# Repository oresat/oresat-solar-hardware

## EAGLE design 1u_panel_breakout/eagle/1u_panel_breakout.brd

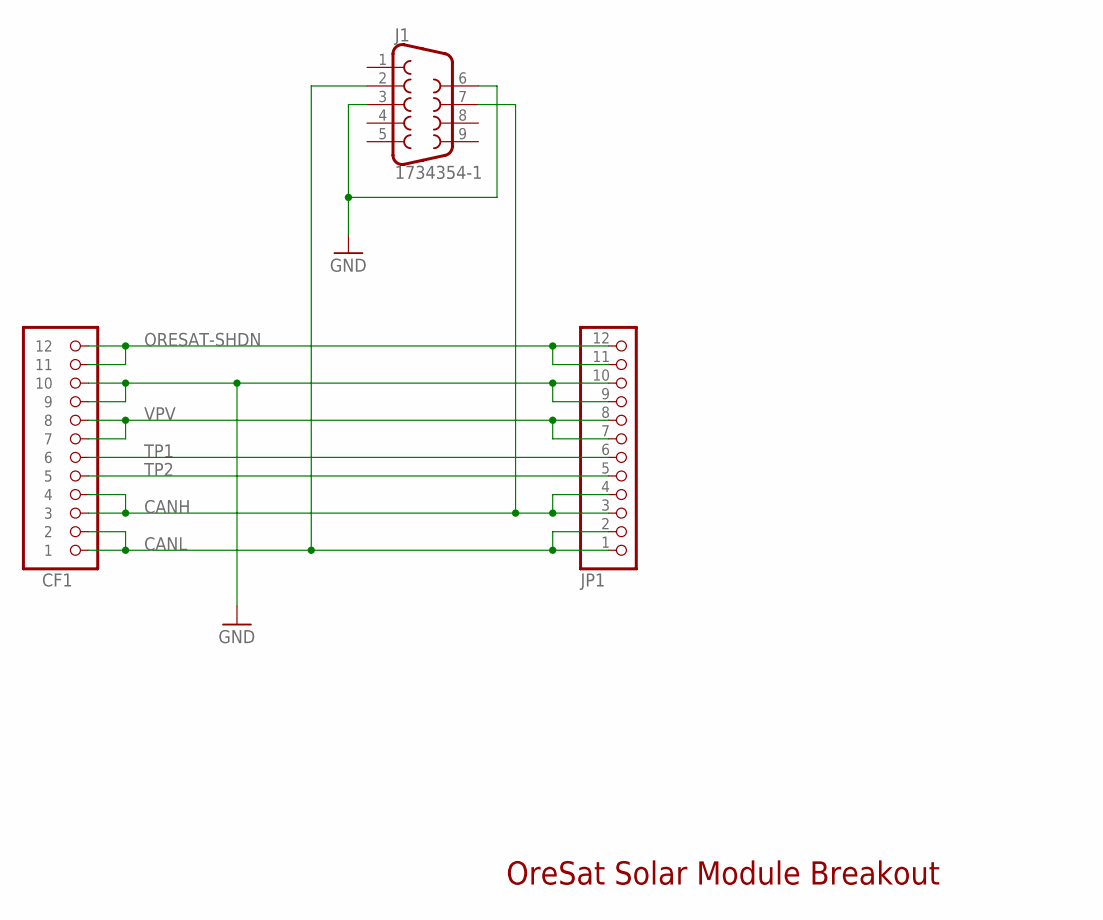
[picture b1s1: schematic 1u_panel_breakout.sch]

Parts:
CF1: ORESAT-SOLARPANEL-12PIN; CON-1.27-F-HARTING-1522012X601XXX
J1: 1734354-1; TE_1734354-1
JP1: PINHD-1X12; 1X12

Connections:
CANH: CF1.3, CF1.4, J1.7, JP1.3, JP1.4
CANL: CF1.1, CF1.2, J1.2, JP1.1, JP1.2
GND: CF1.9, CF1.10, J1.3, J1.6, JP1.9, JP1.10
ORESAT-SHDN: CF1.11, CF1.12, JP1.11, JP1.12
TP1: CF1.6, JP1.6
TP2: CF1.5, JP1.5
VPV: CF1.7, CF1.8, JP1.7, JP1.8

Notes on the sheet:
OreSat Solar Module Breakout

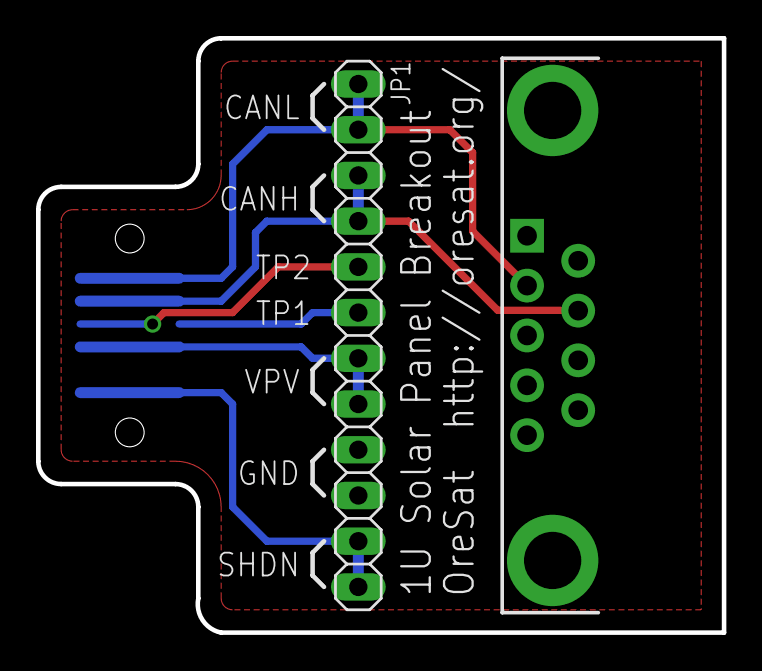
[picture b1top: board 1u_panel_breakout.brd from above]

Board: 2 copper layers, 38.1 x 33.0 mm, 3 parts (1 on the bottom side), 7 nets.

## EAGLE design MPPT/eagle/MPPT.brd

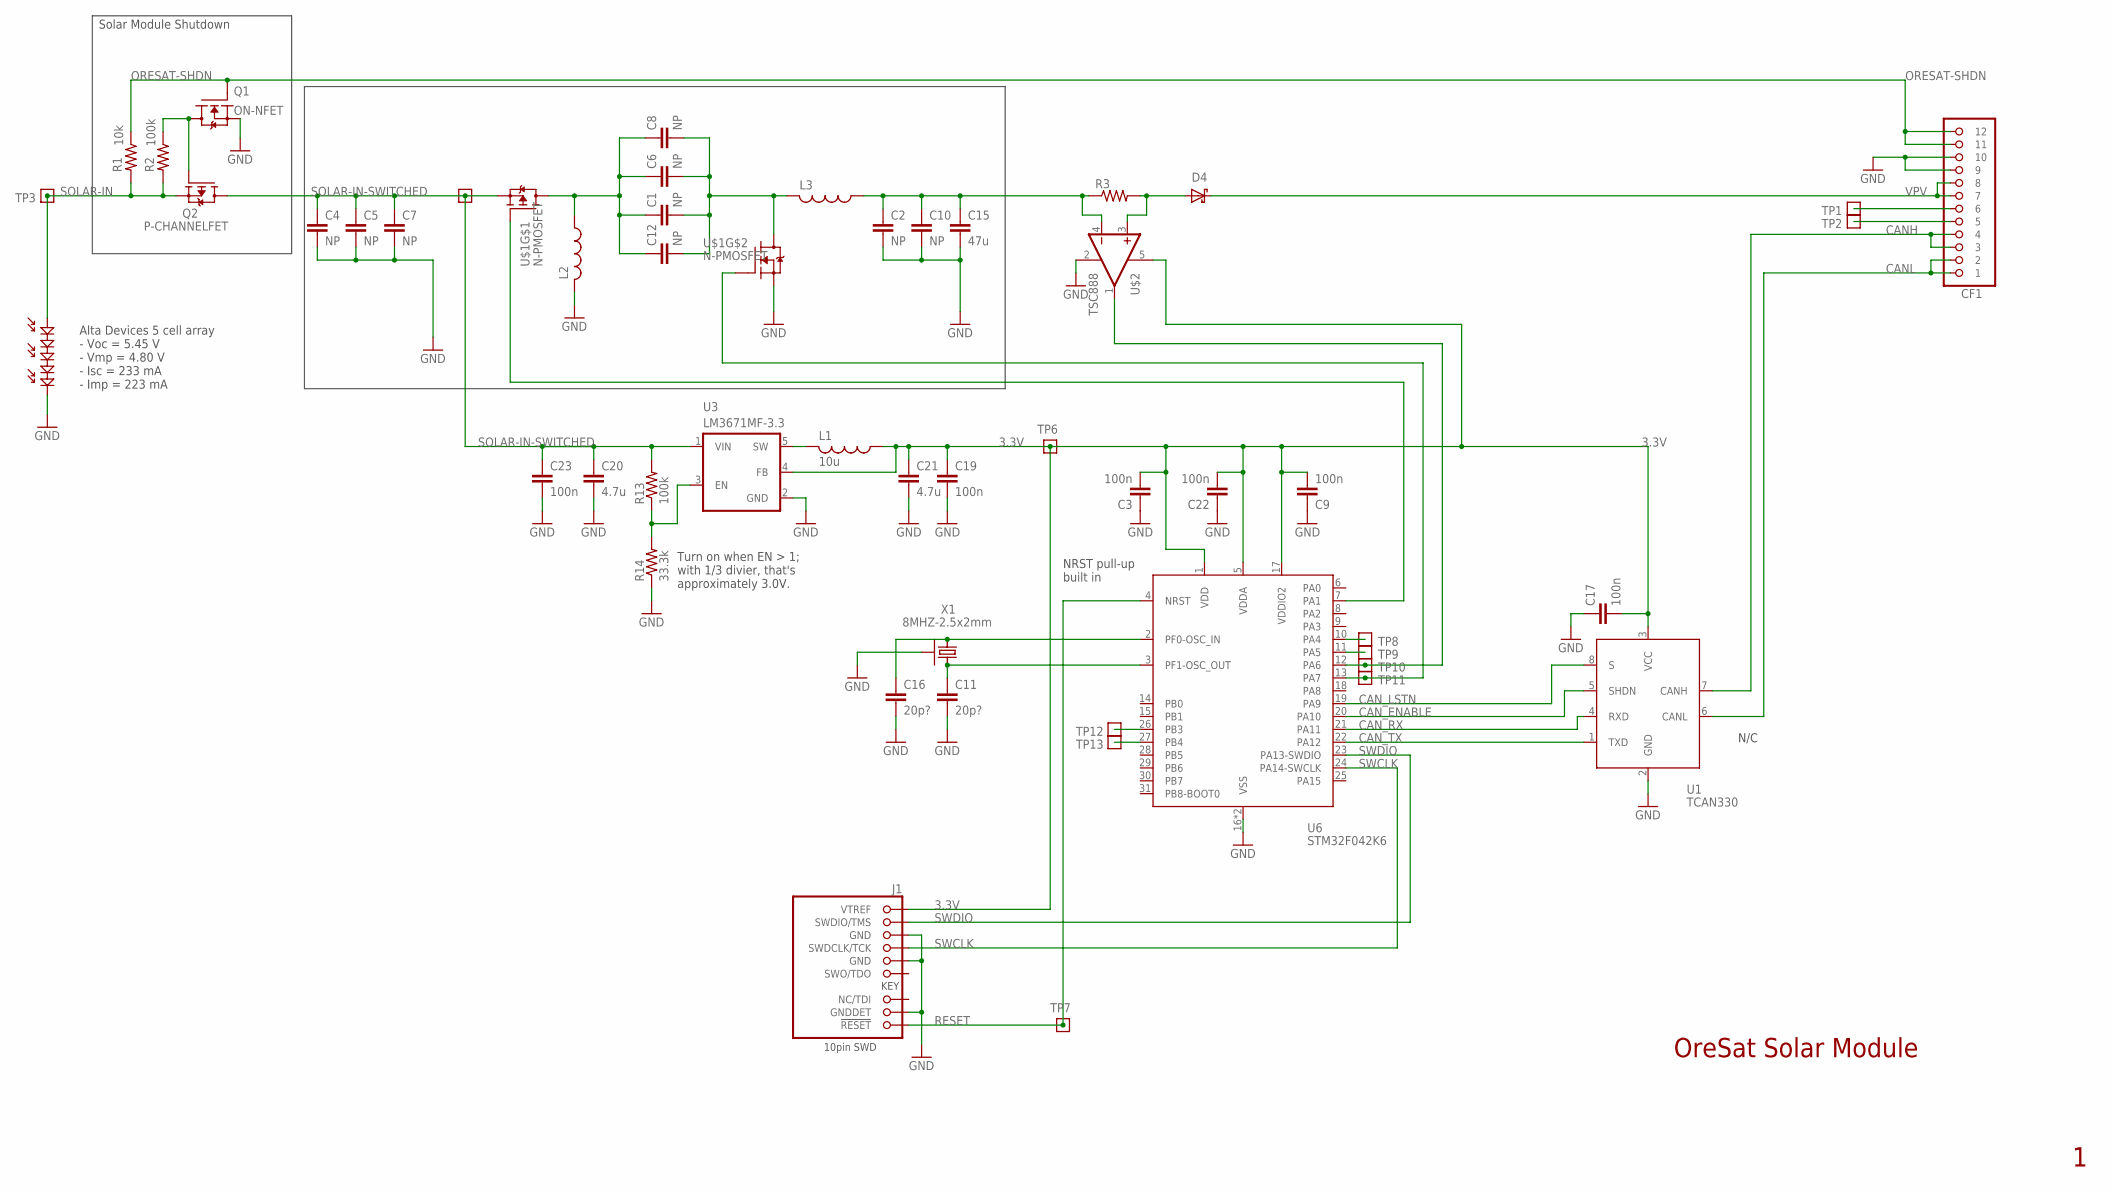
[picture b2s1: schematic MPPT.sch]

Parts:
C1, C2, C4, C5, C6, C7, C8, C10, C12: NP; C0603
C3, C9, C17, C19, C22, C23: 100n; .0402-B-NOSILK
C11, C16: 20p?; .0402-B-NOSILK
C15: 47u; C0603
C20, C21: 4.7u; C0603
CF1: ORESAT-SOLARPANEL-12PIN; CON-1.27-F-HARTING-1522012X601XXX
D2: ALTA-5-CELL-ARRAY; ALTA-FIVE-CELL
D4: SOD123-B SCHOTTKY; SOD123-B
J1: 1.27MM-SWD-CONNECTOR; 1.27MM_2X5
L1: 10u; L2012C
L2, L3: L-USL1812; L1812
Q1: ON-NFET; SOT23
Q2: P-CHANNELFET; SO8
R1: 10k; .0402-B-NOSILK
R2, R13: 100k; .0402-B-NOSILK
R3: R-US_R0603; R0603
R14: 33.3k; .0402-B-NOSILK
TP1, TP2, TP3, TP4, TP6, TP7, TP8, TP9, TP10, TP11, TP12, TP13: TEST-POINT; 2MM-TEST-POINT
U1: TCAN330; SOT23-8_TI-DCN
U3: LM3671MF-3.3; SOT23-5
U6: STM32F042K6; QFP32-7X7
U$1: N-PMOSFET; 5X6POWERFLAT
U$2: TSC888; SOT23-5
X1: 8MHZ-2.5x2mm; CRYSTAL_2.5X2

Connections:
3.3V: C3.2, C9.2, C17.2, C19.1, C21.1, C22.2, J1.VTREF, L1.1, TP6.1, U1.3 (VCC), U3.4 (FB), U6.1 (VDD), U6.5 (VDDA), U6.17 (VDDIO2), U$2.5 (V+)
CANH: CF1.3, CF1.4, U1.7 (CANH)
CANL: CF1.1, CF1.2, U1.6 (CANL)
CAN_ENABLE: U1.5 (SHDN), U6.20 (PA10)
CAN_LSTN: U1.8 (S), U6.19 (PA9)
CAN_RX: U1.4 (RXD), U6.21 (PA11)
CAN_TX: U1.1 (TXD), U6.22 (PA12)
CRYSTALIN: C16.1, U6.2 (PF0-OSC_IN), X1.1
CRYSTALOUT: C11.1, U6.3 (PF1-OSC_OUT), X1.3 (2)
GND: C2.2, C3.1, C4.2, C5.2, C7.2, C9.1, C10.2, C11.2, C15.2, C16.2, C17.1, C19.2, C20.2, C21.2, C22.1, C23.2, CF1.9, CF1.10, D2.NEG, J1.GND, J1.GND@2 (GND), J1.GNDDET, L2.2, Q1.2 (S), R14.1, U1.2 (GND), U3.2 (GND), U6.16 (VSS), U6.32 (VSS), U$1.S2 (S), U$2.2 (GND), X1.2 (SHIELD), X1.4 (SHIELD)
N6: Q1.3 (D), Q2.4 (G), R2.1
unnamed: C1.1, C6.1, C8.1, C12.1, L2.1, U$1.D1 (D), U$1.D11 (D), U$1.D12 (D), U$1.D13 (D), U$1.D14 (D)
unnamed: C1.2, C6.2, C8.2, C12.2, L3.2, U$1.D2 (D), U$1.D21 (D), U$1.D22 (D), U$1.D23 (D), U$1.D24 (D)
unnamed: CF1.6, TP1.1
unnamed: CF1.5, TP2.1
unnamed: TP8.1, U6.10 (PA4)
unnamed: TP9.1, U6.11 (PA5)
unnamed: TP10.1, U6.12 (PA6), U$2.1 (OUT)
unnamed: TP11.1, U6.13 (PA7), U$1.G2 (G)
unnamed: TP12.1, U6.26 (PB3)
unnamed: TP13.1, U6.27 (PB4)
unnamed: C2.1, C10.1, C15.1, L3.1, R3.1, U$2.4 (-IN)
unnamed: U6.7 (PA1), U$1.G1 (G)
unnamed: D4.A (ANODE), R3.2, U$2.3 (+IN)
ORESAT-SHDN: CF1.11, CF1.12, Q1.1 (G), R1.1
RESET: J1.!RESET, TP7.1, U6.4 (NRST)
SOLAR-IN: D2.POS, Q2.1 (S), Q2.2 (S), Q2.3 (S), R1.2, R2.2, TP3.1
SOLAR-IN-SWITCHED: C4.1, C5.1, C7.1, C20.1, C23.1, Q2.5 (D), Q2.6 (D), Q2.7 (D), Q2.8 (D), R13.2, TP4.1, U3.1 (VIN), U$1.S1 (S)
STEPD: L1.2, U3.5 (SW)
SWCLK: J1.SWDCLK (SWDCLK/TCK), U6.24 (PA14-SWCLK)
SWDIO: J1.SWDIO (SWDIO/TMS), U6.23 (PA13-SWDIO)
VDIV: R13.1, R14.2, U3.3 (EN)
VPV: CF1.7, CF1.8, D4.K (CATHODE)

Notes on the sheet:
Alta Devices 5 cell array - Voc = 5.45 V - Vmp = 4.80 V - Isc = 233 mA - Imp = 223 mA
N/C
NRST pull-up built in
Turn on when EN > 1; with 1/3 divier, that's approximately 3.0V.
OreSat Solar Module
Solar Module Shutdown

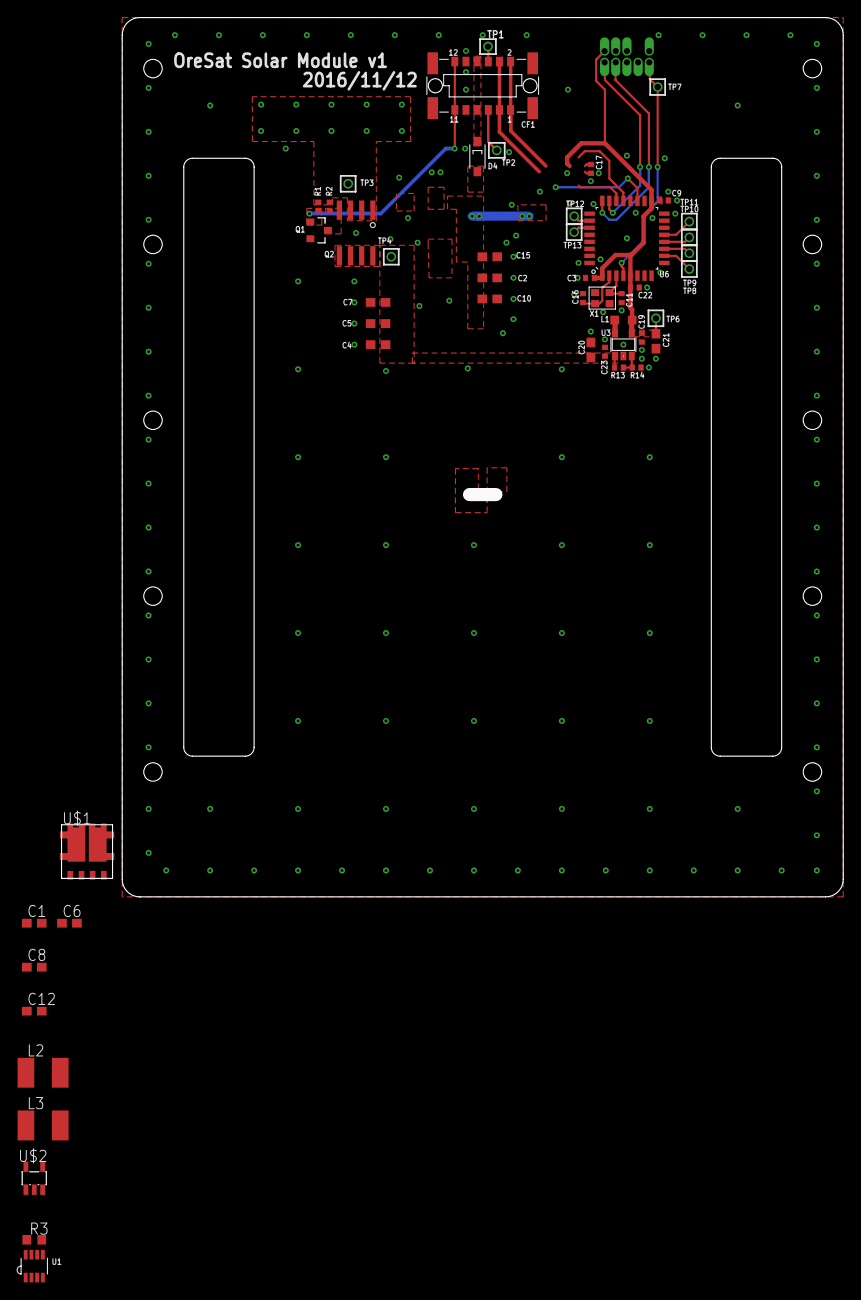
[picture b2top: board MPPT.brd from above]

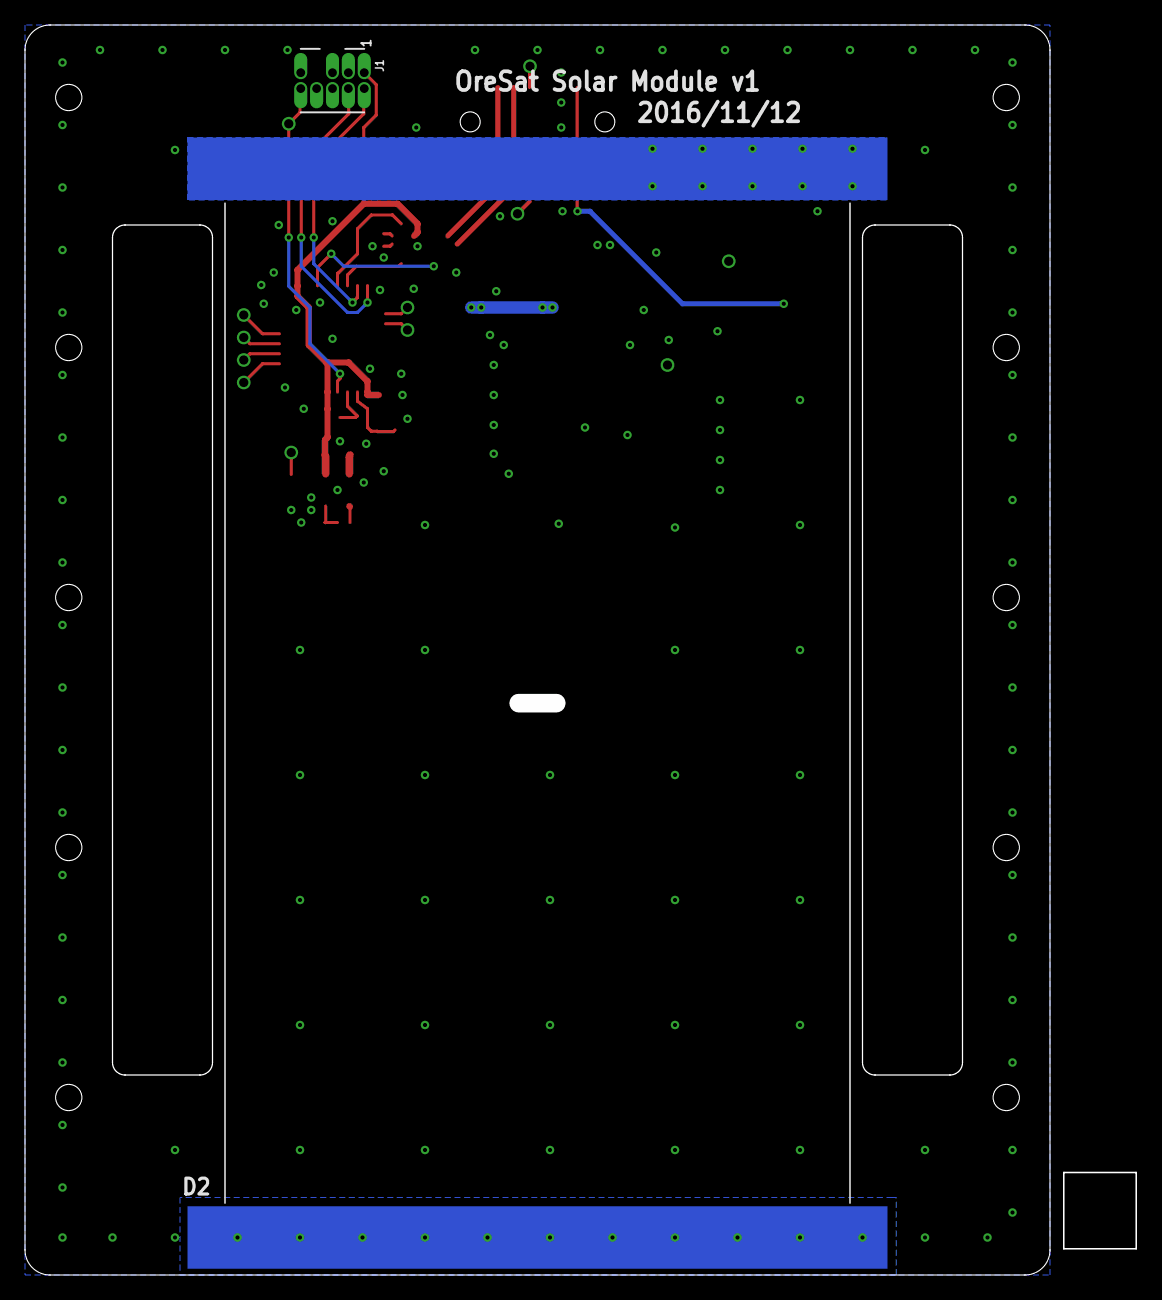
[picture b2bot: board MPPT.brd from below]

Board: 2 copper layers, 88.9 x 100.0 mm, 52 parts (2 on the bottom side), 33 nets.

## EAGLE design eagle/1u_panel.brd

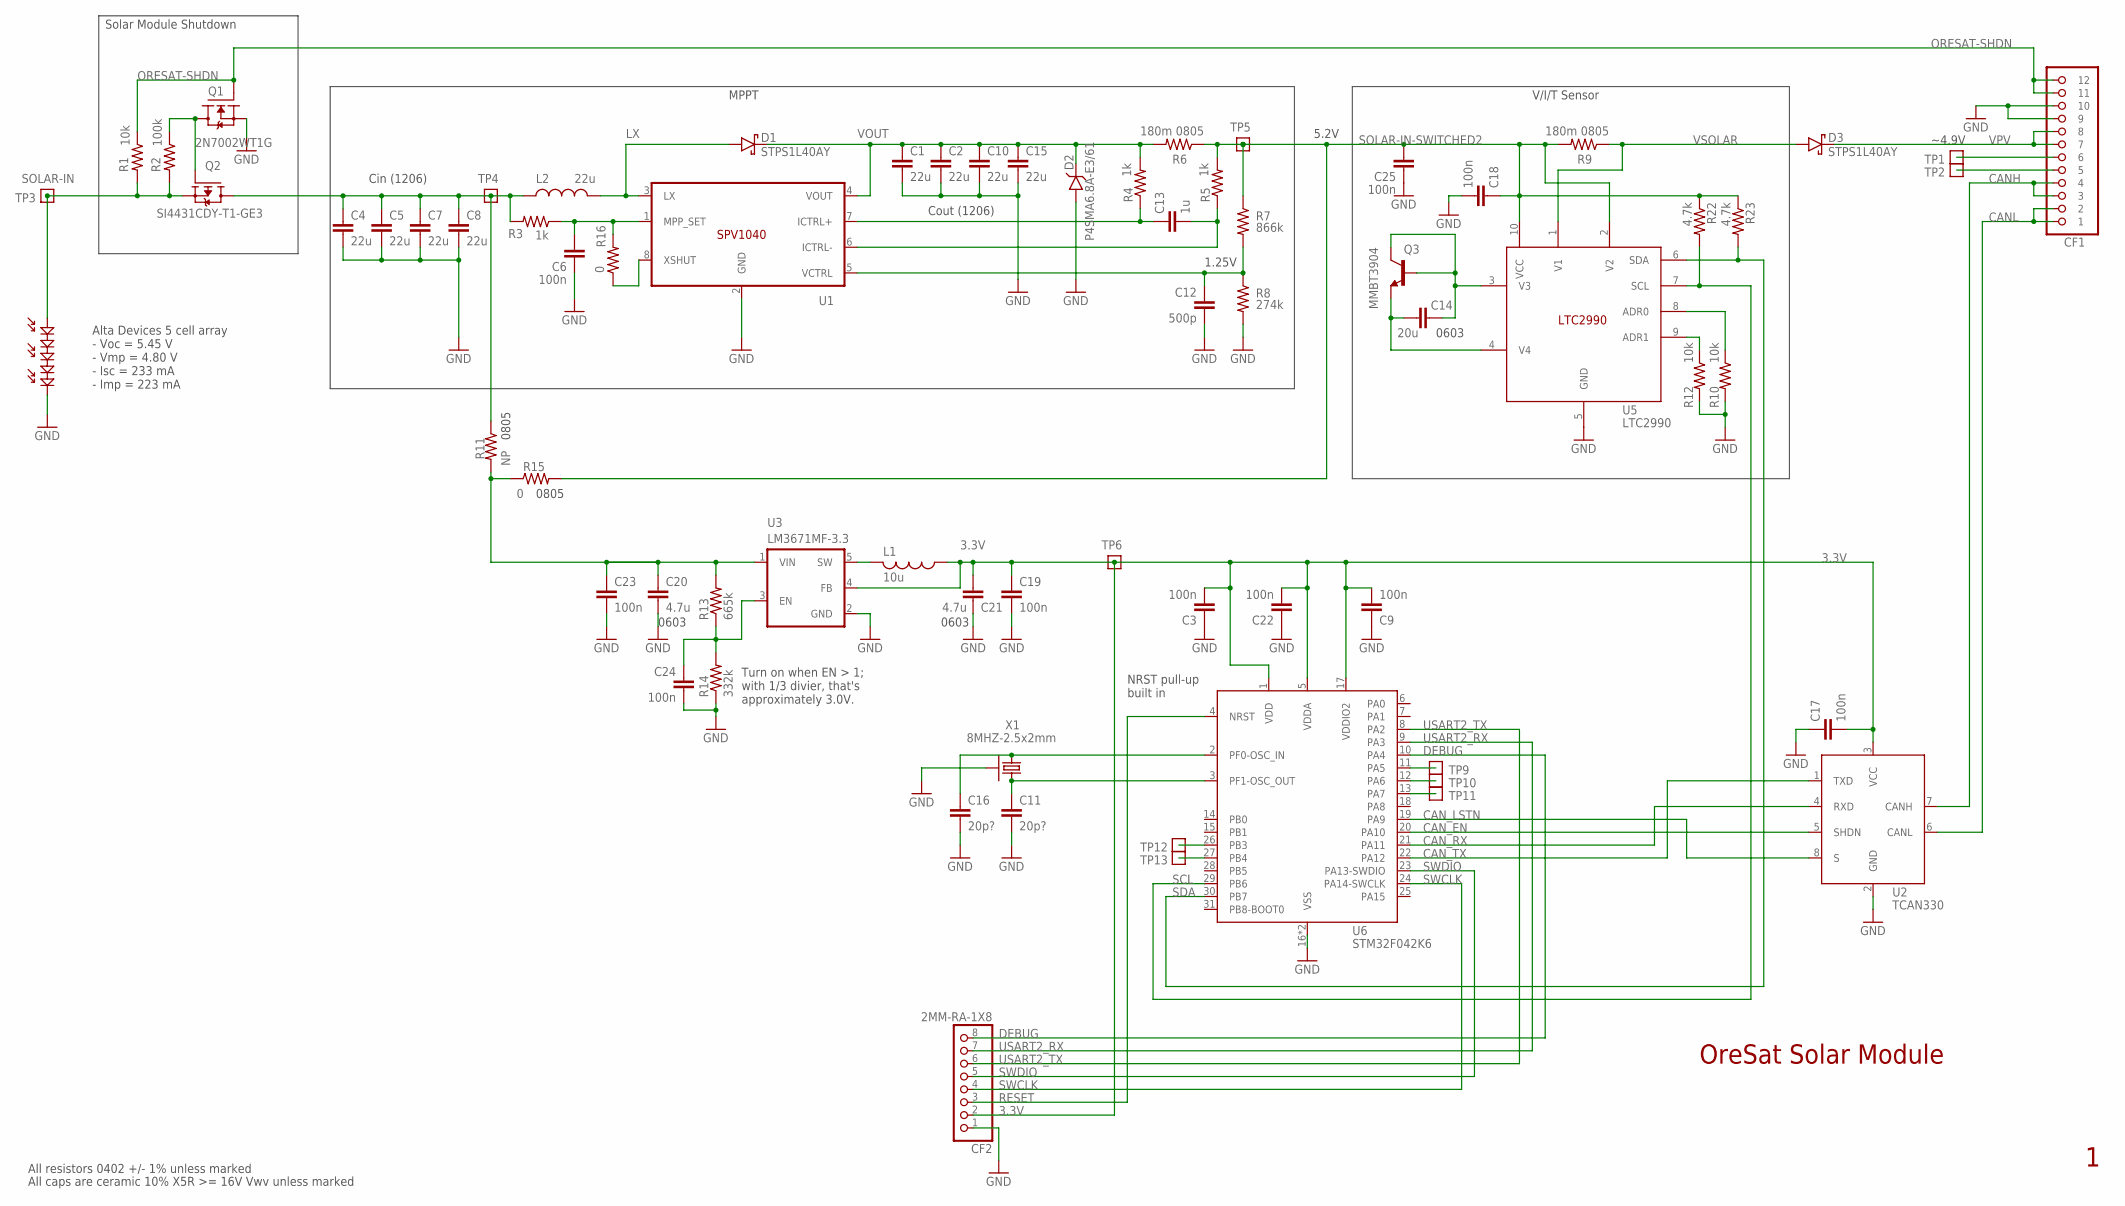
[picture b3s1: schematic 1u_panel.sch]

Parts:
C1, C2, C4, C5, C7, C8, C10, C15: 22u; 1206-B; MPN GRM31CR71A226KE15L
C3, C6, C9, C17, C18, C19, C22, C23, C24, C25: 100n; .0402-B-NOSILK; MPN CL05B104KO5NNNC
C11, C16: 20p?; .0402-B-NOSILK
C12: 500p; .0402-B-NOSILK; MPN CL05B561KB5NNNC
C13: 1u; .0402-B-NOSILK; MPN CL05A105KA5NQNC
C14: 20u; .0603-B-NOSILK; MPN CL10A226MP8NUNE
C20, C21: 4.7u; C0603; MPN CL05B104KO5NNNC
CF1: ORESAT-SOLARPANEL-12PIN; CON-1.27-F-HARTING-1522012X601XXX
CF2: 2MM-RA-1X8; CF-2MM-RA-1X8-PRECIDIP-831; MPN 831-87-050-40-001101
D1, D3: STPS1L40AY; DO214AC; MPN STPS1L40AY
D2: P4SMA6.8A-E3/61; DO214AC; MPN P4SMA6.8A-E3/61
L1: 10u; L2012C; MPN CB2012T100KR
L2: 22u; VISHAY-DALE-IFSR-1515AHER; MPN IFSC1515AHER220M01
PV1: ALTA-5-CELL-ARRAYALTA-FIVE-CELL-SLOT; ALTA-FIVE-CELL-THROUGH-SLOT
Q1: 2N7002WT1G; SOT23; MPN 2N7002WT1G
Q2: SI4431CDY-T1-GE3; SO8; MPN SI4431CDY-T1-GE3
Q3: MMBT3904; SOT23HOLE; MPN MMBT3904
R1, R10, R12: 10k; .0402-B-NOSILK; MPN MCR01MZPF1002
R2: 100k; .0402-B-NOSILK; MPN MCR01MRTF1003
R3: 1k; .0402-B-NOSILK; MPN MCR01MZPF1001
R4, R5: 1k; .0402-B-NOSILK
R6, R9: 180m 0805; .0805-B-NOSILK; MPN RCWE0805R180FKEA
R7: 866k; .0402-B-NOSILK; MPN RC1005F8663CS
R8: 274k; .0402-B-NOSILK; MPN CRCW0402274KFKED
R11: NP; .0805-B-NOSILK
R13: 665k; .0402-B-NOSILK; MPN RC1005F6653CS
R14: 332k; .0402-B-NOSILK; MPN RC1005F3323CS
R15: 0; .0805-B-NOSILK
R16: 0; .0402-B-NOSILK
R22, R23: 4.7k; .0402-B-NOSILK; MPN TRR01MZPF4701
TP1, TP2, TP3, TP4, TP5, TP6, TP9, TP10, TP11, TP12, TP13: TEST-POINT; 2MM-TEST-POINT
U1: SPV1040; TSSOP-8; MPN SPV1040T
U2: TCAN330; SOT23-8_TI-DCN; MPN TCAN330GDCNT
U3: LM3671MF-3.3; SOT23-5
U5: LTC2990; MSOP10; MPN LTC2990CMS#PBF
U6: STM32F042K6; QFP32-7X7; MPN STM32F042K6T6
X1: 8MHZ-2.5x2mm; CRYSTAL_2.5X2; MPN ECS-80-18-20BQ-DS

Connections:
3.3V: C3.2, C9.2, C17.2, C19.1, C21.1, C22.2, CF2.2, L1.1, TP6.1, U2.3 (VCC), U3.4 (FB), U6.1 (VDD), U6.5 (VDDA), U6.17 (VDDIO2)
ADDRSELECT: R10.1, U5.8 (ADR0)
ADR1: R12.1, U5.9 (ADR1)
CANH: CF1.3, CF1.4, U2.7 (CANH)
CANL: CF1.1, CF1.2, U2.6 (CANL)
CAN_EN: U2.5 (SHDN), U6.20 (PA10)
CAN_LSTN: U2.8 (S), U6.19 (PA9)
CAN_RX: U2.4 (RXD), U6.21 (PA11)
CAN_TX: U2.1 (TXD), U6.22 (PA12)
CRYSTALIN: C16.1, U6.2 (PF0-OSC_IN), X1.1
CRYSTALOUT: C11.1, U6.3 (PF1-OSC_OUT), X1.3 (2)
DEBUG: CF2.8, U6.10 (PA4)
GND: C1.2, C2.2, C3.1, C4.2, C5.2, C6.1, C7.2, C8.2, C9.1, C10.2, C11.2, C12.2, C15.2, C16.2, C17.1, C18.2, C19.2, C20.2, C21.2, C22.1, C23.2, C24.2, C25.1, CF1.9, CF1.10, CF2.1, D2.A, PV1.NEG1 (NEG), PV1.NEG2 (NEG), Q1.2 (S), R8.2, R10.2, R12.2, R14.1, U1.2 (GND), U2.2 (GND), U3.2 (GND), U5.5 (GND), U6.16 (VSS), U6.32 (VSS), X1.2 (SHIELD), X1.4 (SHIELD)
ICTRL+: C13.2, R4.1, U1.7 (ICTRL+)
ICTRL-: C13.1, R5.1, U1.6 (ICTRL-)
LX: D1.A, L2.1, U1.3 (LX)
MPP-SET: C6.2, R3.1, R16.2, U1.1 (MPP_SET)
N6: Q1.3 (D), Q2.4 (G), R2.1
unnamed: C20.1, C23.1, R11.2, R13.2, R15.1, U3.1 (VIN)
unnamed: CF1.6, TP1.1
unnamed: CF1.5, TP2.1
unnamed: TP9.1, U6.11 (PA5)
unnamed: TP10.1, U6.12 (PA6)
unnamed: TP11.1, U6.13 (PA7)
unnamed: TP12.1, U6.26 (PB3)
unnamed: TP13.1, U6.27 (PB4)
ORESAT-SHDN: CF1.11, CF1.12, Q1.1 (G), R1.1
RESET: CF2.3, U6.4 (NRST)
SCL: R22.2, U5.7 (SCL), U6.29 (PB6)
SDA: R23.2, U5.6 (SDA), U6.30 (PB7)
SOLAR-IN: PV1.POS1 (POS), PV1.POS2 (POS), Q2.1 (S), Q2.2 (S), Q2.3 (S), R1.2, R2.2, TP3.1
SOLAR-IN-SWITCHED: C4.1, C5.1, C7.1, C8.1, L2.2, Q2.5 (D), Q2.6 (D), Q2.7 (D), Q2.8 (D), R3.2, R11.1, TP4.1
SOLAR-IN-SWITCHED2: C18.1, C25.2, R5.2, R6.1, R7.1, R9.2, R15.2, R22.1, R23.1, TP5.1, U5.2 (V2), U5.10 (VCC)
STEPD: L1.2, U3.5 (SW)
SWCLK: CF2.4, U6.24 (PA14-SWCLK)
SWDIO: CF2.5, U6.23 (PA13-SWDIO)
USART2_RX: CF2.7, U6.9 (PA3)
USART2_TX: CF2.6, U6.8 (PA2)
V3: C14.2, Q3.1 (B), Q3.3 (C), U5.3 (V3)
V4: C14.1, Q3.2 (E), U5.4 (V4)
VCTRL: C12.1, R7.2, R8.1, U1.5 (VCTRL)
VDIV: C24.1, R13.1, R14.2, U3.3 (EN)
VOUT: C1.1, C2.1, C10.1, C15.1, D1.C, D2.C, R4.2, R6.2, U1.4 (VOUT)
VPV: CF1.7, CF1.8, D3.C
VSOLAR: D3.A, R9.1, U5.1 (V1)
XSHUT: R16.1, U1.8 (XSHUT)

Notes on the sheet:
Alta Devices 5 cell array - Voc = 5.45 V - Vmp = 4.80 V - Isc = 233 mA - Imp = 223 mA
NRST pull-up built in
Turn on when EN > 1; with 1/3 divier, that's approximately 3.0V.
OreSat Solar Module
V/I/T Sensor
Solar Module Shutdown
MPPT
All resistors 0402 +/- 1% unless marked
All caps are ceramic 10% X5R >= 16V Vwv unless marked
Cin (1206)
Cout (1206)
5.2V
0603
0805
~4.9V
1.25V

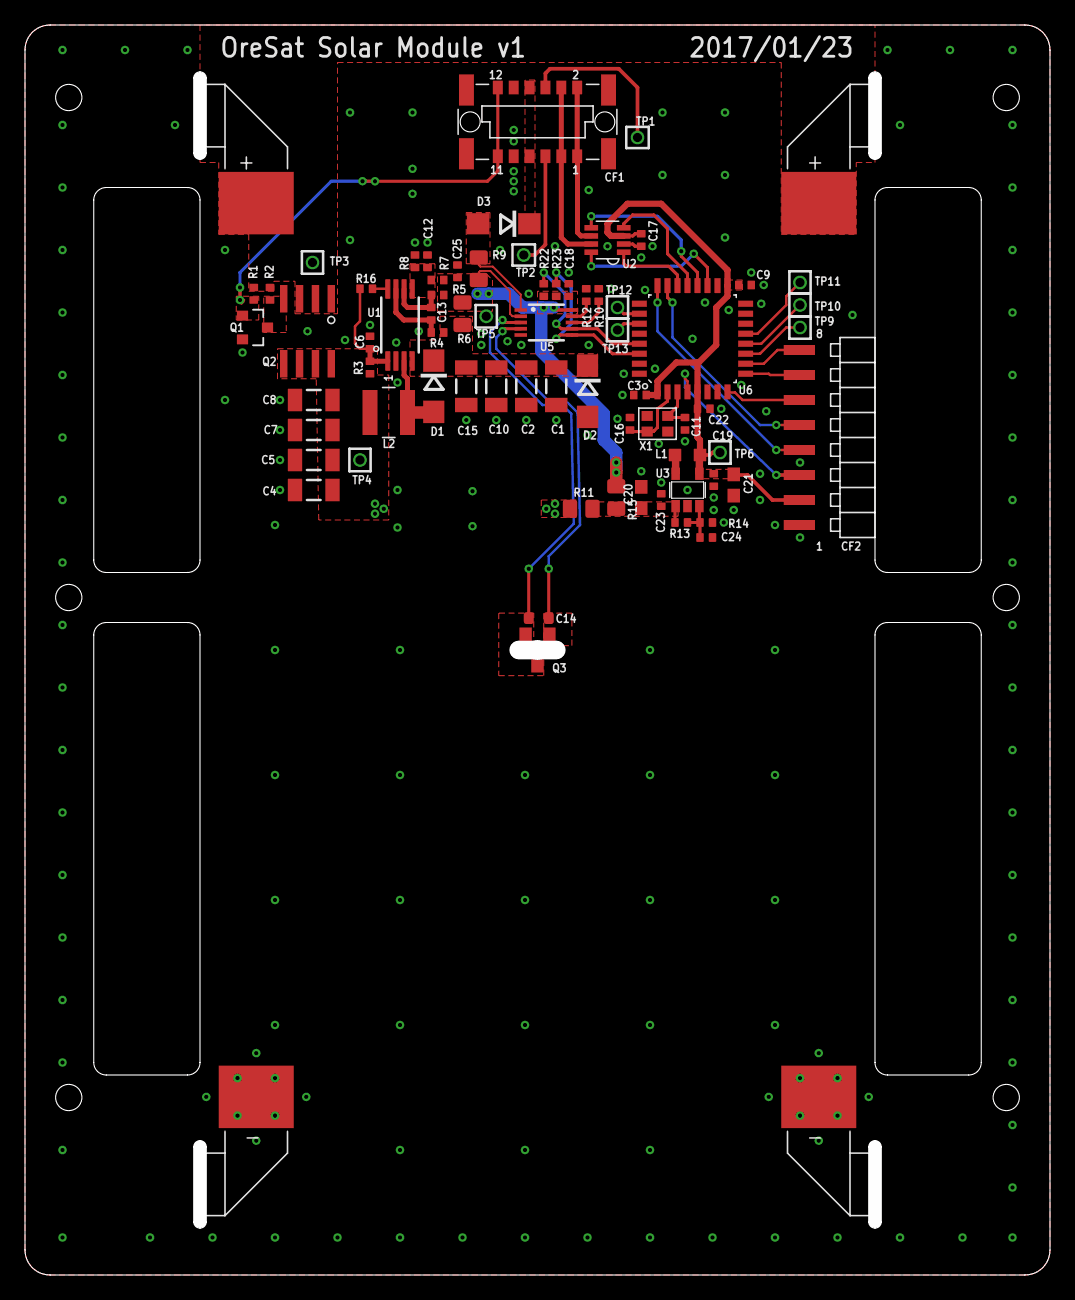
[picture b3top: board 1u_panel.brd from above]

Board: 2 copper layers, 82.0 x 100.0 mm, 71 parts (1 on the bottom side), 46 nets.
